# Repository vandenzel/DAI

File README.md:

# DAI

Stuff regarding the DAIpc and related systems

Check the different directories for README's and other clues to what they are about.

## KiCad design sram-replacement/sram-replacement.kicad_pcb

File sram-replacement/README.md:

# sram-replacement

The 2111 Static RAM chips (IC74 and IC75) seem to fail easily, but are really expensive to replace.

I've taken the hint from [Bruno Vivien](http://bruno.vivien.pagesperso-orange.fr/DAI/reparation/panne1.htm) and created my own version of a similar workaround.

I used a 6116 SRAM chip (2k x 8bits), which is way overkill, but meh, cheap enough.

I might be tempted to design a X-Bus card that replaces all the SRAM and DRAM of the system with one 64 Kbyte SRAM chips (or maybe two 32 Kbyte SRAM chips), and a bit of glue logic to avoid the ROM and device area's

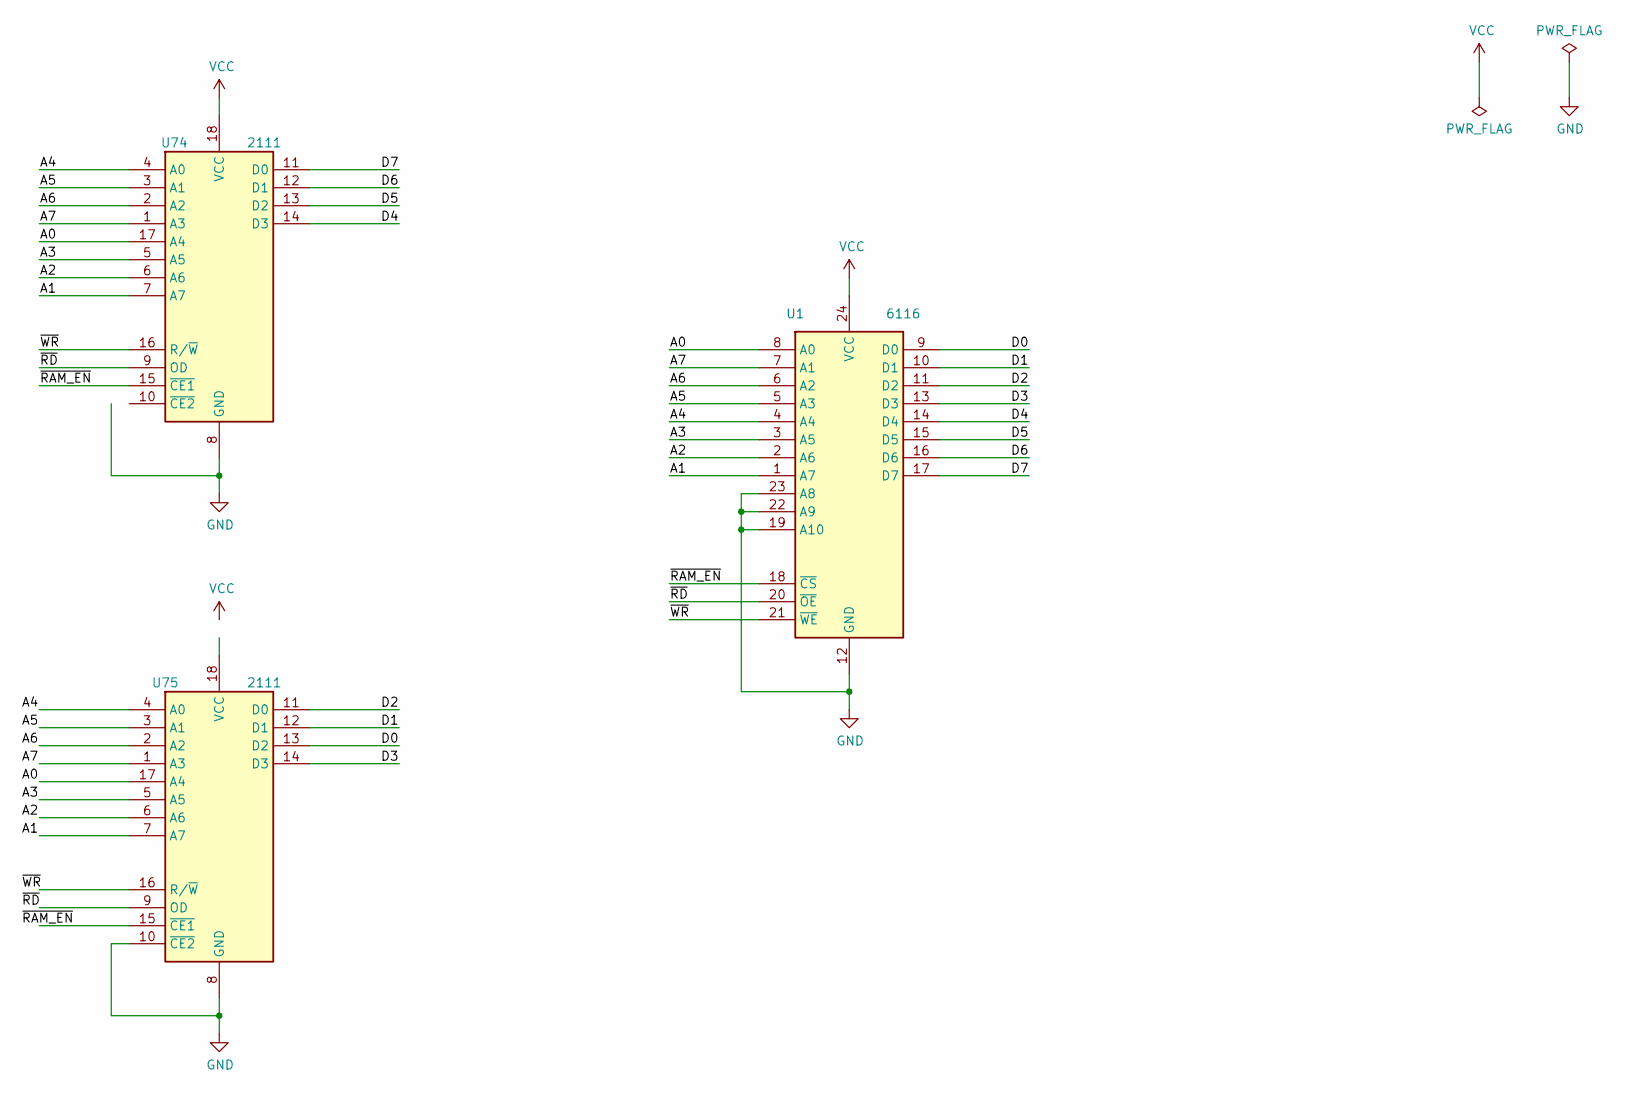
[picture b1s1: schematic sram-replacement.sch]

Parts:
U1: 6116; SOIC-24W_7.5x15.4mm_P1.27mm
U74, U75: 2111; DIP-18_W7.62mm_LongPads

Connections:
/A0: U1.8 (A0), U74.17 (A4)
/A1: U1.1 (A7), U74.7 (A7)
/A2: U1.2 (A6), U74.6 (A6)
/A3: U1.3 (A5), U74.5 (A5)
/A4: U1.4 (A4), U74.4 (A0)
/A5: U1.5 (A3), U74.3 (A1)
/A6: U1.6 (A2), U74.2 (A2)
/A7: U1.7 (A1), U74.1 (A3)
/D0: U1.9 (D0), U75.13 (D2)
/D1: U1.10 (D1), U75.12 (D1)
/D2: U1.11 (D2), U75.11 (D0)
/D3: U1.13 (D3), U75.14 (D3)
/D4: U1.14 (D4), U74.14 (D3)
/D5: U1.15 (D5), U74.13 (D2)
/D6: U1.16 (D6), U74.12 (D1)
/D7: U1.17 (D7), U74.11 (D0)
/~RAM_EN: U1.18 (~CS), U74.15 (~CE1)
/~RD: U1.20 (~OE), U74.9 (OD)
/~WR: U1.21 (~WE), U74.16 (R/~W)
GND: U1.12 (GND), U1.19 (A10), U1.22 (A9), U1.23 (A8), U74.8 (GND), U75.8 (GND), U75.10 (~CE2)
VCC: U1.24 (VCC), U74.18 (VCC)

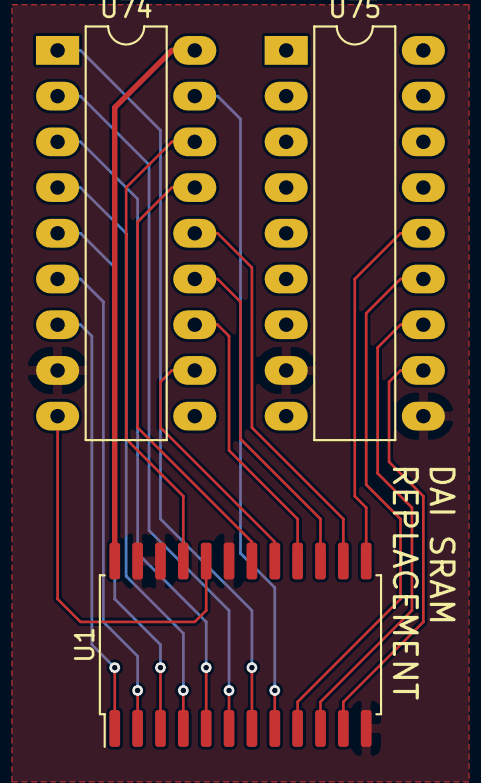
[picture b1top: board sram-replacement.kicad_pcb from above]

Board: 2 copper layers, 3 parts (0 on the bottom side), 21 nets.

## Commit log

2021-02-09 initial
2021-02-09 added kicad-lib
2021-02-09 added sram-replacement
2021-02-09 added rom-card
2021-02-09 added rgb-card
2021-02-09 added dci-interface
2021-02-09 added some explanatory readmes
2021-02-09 small bugfix in prom.md
